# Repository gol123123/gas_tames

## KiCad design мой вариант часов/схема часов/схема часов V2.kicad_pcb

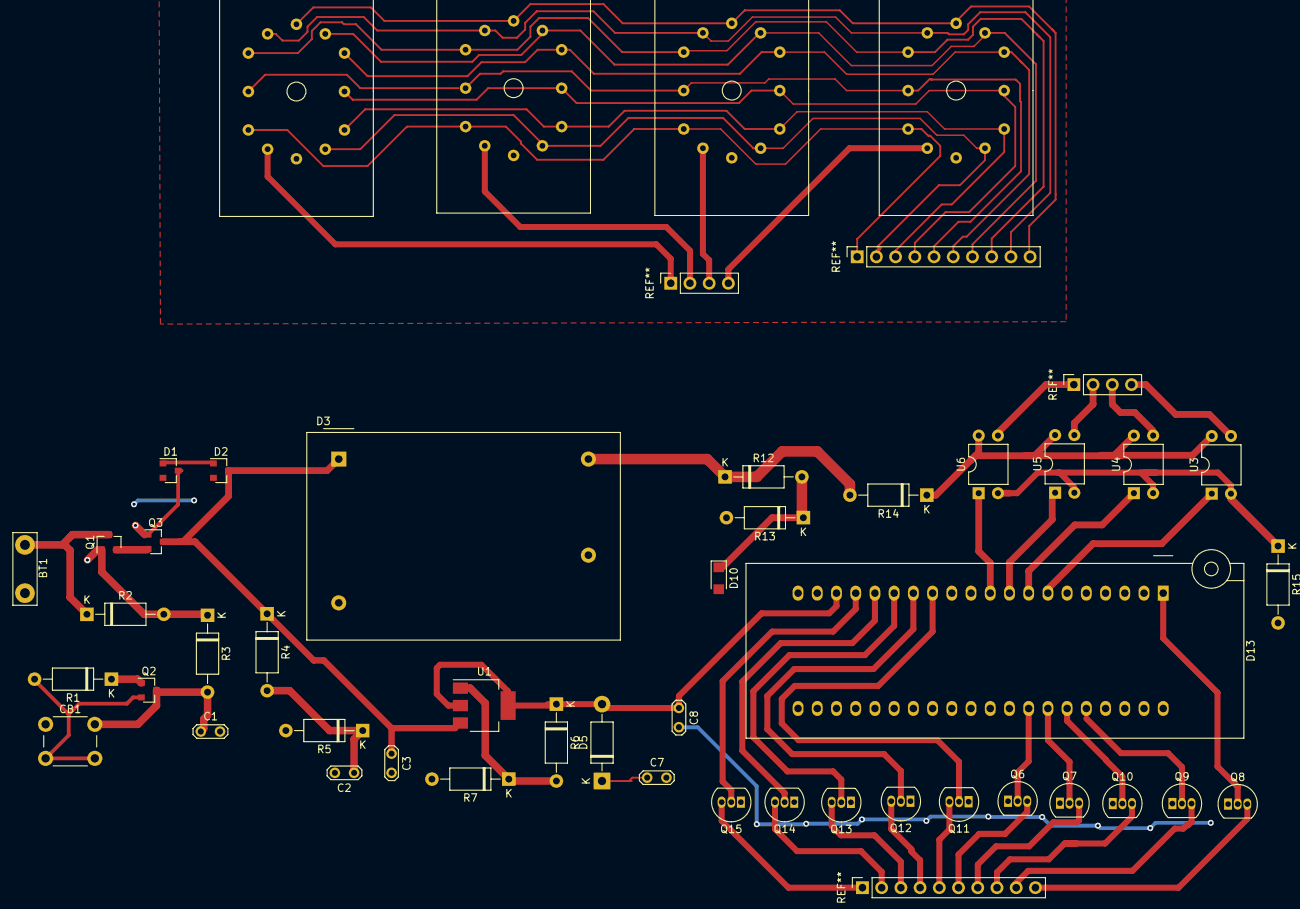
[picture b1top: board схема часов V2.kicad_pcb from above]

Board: 2 copper layers, 46 parts (0 on the bottom side), 43 nets.

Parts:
BT1: Battery_Cell; TestPoint_Bridge_Pitch6.35mm_Drill1.3mm
C1, C2: 100n; TestPoint_2Pads_Pitch2.54mm_Drill0.8mm
C3: 0.1u; TestPoint_2Pads_Pitch2.54mm_Drill0.8mm
C7: 10u; TestPoint_2Pads_Pitch2.54mm_Drill0.8mm
C8: 1u; TestPoint_2Pads_Pitch2.54mm_Drill0.8mm
CB1: CircuitBreaker_1P; SW_PUSH_6mm_H9.5mm
D1, D2: BAT54C; SOT-23
D3: dc-ac_180v; Converter_ACDC_TRACO_TMG-15_THT
D5: 1N4002; D_DO-41_SOD81_P10.16mm_Horizontal
D9, D11, D12, D14: in-12a; IN12
D10: BZD27Cxx; D_SMF
D13: stm32; DIP_Socket-40_W11.9_W12.7_W15.24_W17.78_W18.5_3M_240-1280-0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
Q1, Q3: IRLML6402; SOT-23
Q2: BSS123; SOT-23
Q6, Q7, Q8, Q9, Q10, Q11, Q12, Q13, Q14, Q15: MPSA42; TO-92_Inline
R1, R3, R4, R5: 10k; D_A-405_P10.16mm_Horizontal
R2: 200k; D_A-405_P10.16mm_Horizontal
R6: 4k; D_A-405_P10.16mm_Horizontal
R7: 11k; D_A-405_P10.16mm_Horizontal
R12: 177k; D_A-405_P10.16mm_Horizontal
R13: 3k; D_A-405_P10.16mm_Horizontal
R14: 72k; D_A-405_P10.16mm_Horizontal
R15: 470; D_A-405_P10.16mm_Horizontal
U1: LM317_SOT-223; SOT-223-3_TabPin2
U3, U4, U5, U6: TLP627; DIP-4_W7.62mm

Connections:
+12C: D1.1, D2.1
/KEY: Q2.1, R1.1
/P_PUT: C2.1, R4.2, R5.1
/V: C8.1, D5.2, D13.18, R6.1, U1.2
/V_IND: D10.1, D13.25, R12.2, R13.1
/X0: D13.17, Q15.2
/X1: D13.33, Q6.2
/X2: D13.34, Q7.2
/X3: D13.1, Q8.2
/X4: D13.36, Q9.2
/X5: D13.35, Q10.2
/X6: D13.13, Q11.2
/X7: D13.14, Q12.2
/X8: D13.15, Q13.2
/X9: D13.16, Q14.2
/Y2: D13.8, U4.1
/Y3: D13.9, U5.1
/Y4: D13.10, U6.1
GND: C1.2, C2.2, C3.2, C7.2, C8.2, CB1.2, D1.2, D2.2, D3.2, D3.4, D10.2, D13.19, Q2.2, Q6.1, Q7.1, Q8.1, Q9.1, Q10.1, Q11.1, Q12.1, Q13.1, Q14.1, Q15.1, R1.2, R5.2, R7.2, R13.2, R15.2
unnamed: BT1.1, Q1.3, R2.1
unnamed: C1.1, CB1.1, Q2.3, R3.2
unnamed: C3.1, D2.3, D3.1, Q3.3, R4.1, U1.3
unnamed: C7.1, D5.1
unnamed: D1.3, Q1.1, Q3.1, R2.2, R3.1
unnamed: D3.3, R12.1, R14.2
unnamed: D9.1, U6.3
unnamed: D11.1, U5.3
unnamed: D9.2, D11.2, D12.2, D14.2, Q15.3
unnamed: D9.3, D11.3, D12.3, D14.3, Q14.3
unnamed: D9.4, D11.4, D12.4, D14.4, Q13.3
unnamed: D9.5, D11.5, D12.5, D14.5, Q12.3
unnamed: D9.6, D11.6, D12.6, D14.6, Q11.3
unnamed: D9.7, D11.7, D12.7, D14.7, Q10.3
unnamed: D9.8, D11.8, D12.8, D14.8, Q9.3
unnamed: D9.9, D11.9, D12.9, D14.9, Q8.3
unnamed: D9.10, D11.10, D12.10, D14.10, Q7.3
unnamed: D9.11, D11.11, D12.11, D14.11, Q6.3
unnamed: D12.1, U4.3
unnamed: D14.1, U3.3
unnamed: Q1.2, Q3.2
unnamed: R6.2, R7.1, U1.1
unnamed: R14.1, U3.4, U4.4, U5.4, U6.4
unnamed: D13.7, R15.1, U3.1, U3.2, U4.2, U5.2, U6.2

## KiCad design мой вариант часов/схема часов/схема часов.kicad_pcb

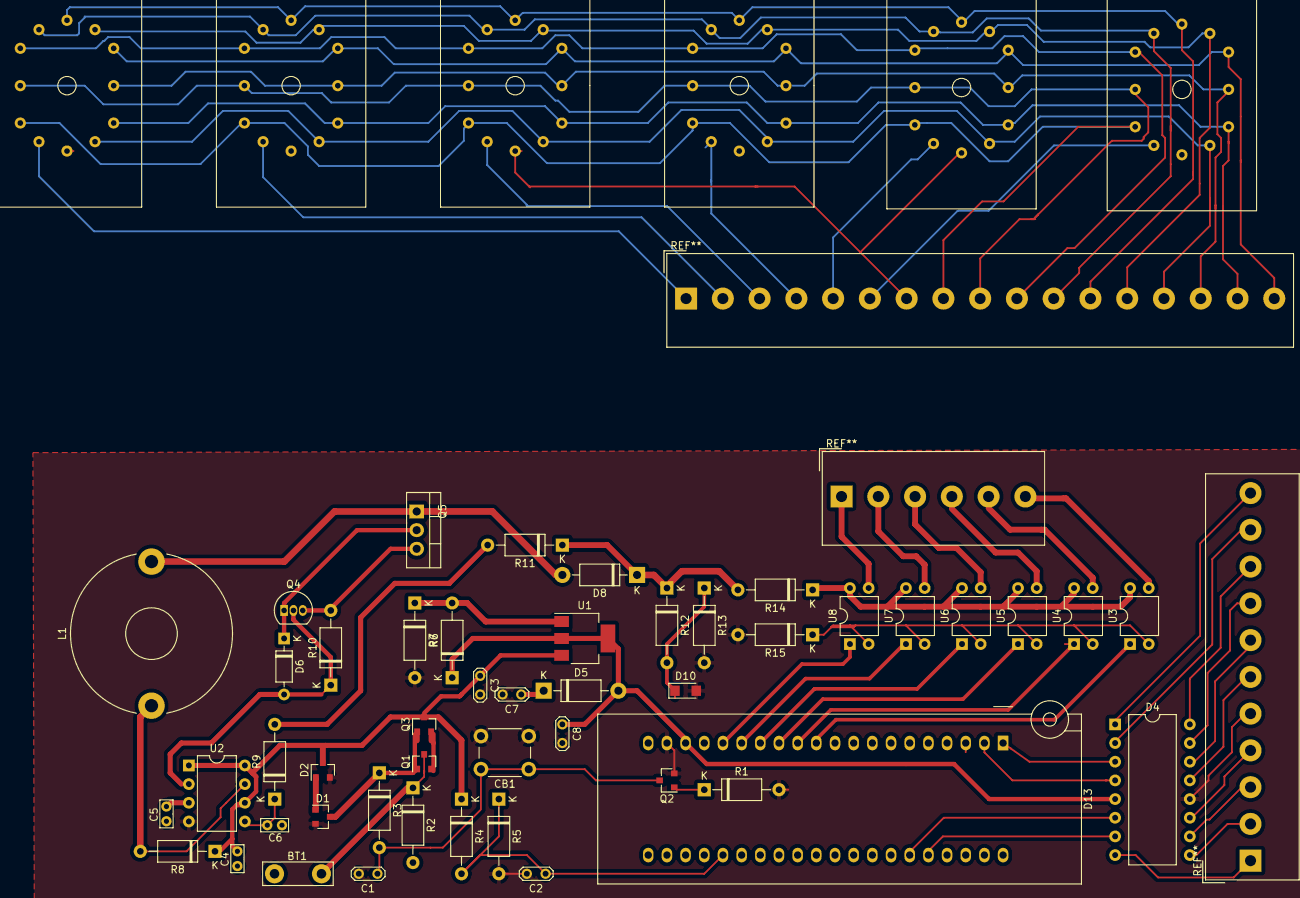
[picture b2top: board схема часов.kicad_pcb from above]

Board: 2 copper layers, 53 parts (0 on the bottom side), 39 nets.

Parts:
BT1: Battery_Cell; TestPoint_Bridge_Pitch6.35mm_Drill1.3mm
C1, C2: 100n; TestPoint_2Pads_Pitch2.54mm_Drill0.8mm
C3: 0.1u; TestPoint_2Pads_Pitch2.54mm_Drill0.8mm
C4: 1000u; TestPoint_Bridge_Pitch2.0mm_Drill0.7mm
C5, C6: 1n; TestPoint_Bridge_Pitch2.0mm_Drill0.7mm
C7: 10u; TestPoint_2Pads_Pitch2.54mm_Drill0.8mm
C8: 1u; TestPoint_2Pads_Pitch2.54mm_Drill0.8mm
CB1: CircuitBreaker_1P; SW_PUSH_6mm_H9.5mm
D1, D2: BAT54C; SOT-23
D3, D7, D9, D11, D12, D14: in-12a; IN12
D4: SN74141N; DIP-16_W10.16mm
D5: 1N4002; D_DO-41_SOD81_P10.16mm_Horizontal
D6: 1N4148; D_DO-35_SOD27_P7.62mm_Horizontal
D8: 1N4007; D_DO-41_SOD81_P10.16mm_Horizontal
D10: BZD27Cxx; D_SMF
D13: stm32; DIP_Socket-40_W11.9_W12.7_W15.24_W17.78_W18.5_3M_240-1280-0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
L1: 230; L_Toroid_Horizontal_D21.8mm_P19.60mm_Bourns_2100
Q1, Q3: IRLML6402; SOT-23
Q2: BSS123; SOT-23
Q4: 2N3906; TO-92_Inline
Q5: IRF840; TO-220-3_Vertical
R1, R3, R4, R5, R10: 10k; D_A-405_P10.16mm_Horizontal
R2: 200k; D_A-405_P10.16mm_Horizontal
R6: 4k; D_A-405_P10.16mm_Horizontal
R7: 11k; D_A-405_P10.16mm_Horizontal
R8: 0.2; D_A-405_P10.16mm_Horizontal
R9, R13: 3k; D_A-405_P10.16mm_Horizontal
R11: 430k; D_A-405_P10.16mm_Horizontal
R12: 177k; D_A-405_P10.16mm_Horizontal
R14: 72k; D_A-405_P10.16mm_Horizontal
R15: 470; D_A-405_P10.16mm_Horizontal
U1: LM317_SOT-223; SOT-223-3_TabPin2
U2: MC34063AP; DIP-8_W7.62mm
U3, U4, U5, U6, U7, U8: TLP627; DIP-4_W7.62mm

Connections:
+12C: D1.1, D2.1
/KEY: D13.17, Q2.1, R1.1
/V: C8.1, D4.5, D5.2, D13.18, R6.1, U1.2
/V_IND_OBR: D10.1, D13.26, R12.2, R13.1
/V_type: C2.1, D13.25, R4.2, R5.1
/X2: D4.6, D13.2
/X3: D4.7, D13.3
/X4: D4.4, D13.4
/Y0: D13.11, U3.1
/Y1: D13.12, U4.1
/Y2: D13.13, U5.1
/Y3: D13.14, U6.1
/Y4: D13.15, U7.1
/Y5: D13.16, U8.1
GND: C1.2, C2.2, C3.2, C7.2, C8.2, CB1.2, D1.2, D2.2, D4.12, D10.2, D13.19, Q2.2, R1.2, R5.2, R7.2, R13.2, R15.2, U2.4
unnamed: BT1.1, Q1.3, R2.1
unnamed: C1.1, CB1.1, Q2.3, R3.2
unnamed: C3.1, C4.1, D2.3, Q3.3, R4.1, R8.1, U1.3, U2.1, U2.6, U2.8
unnamed: C5.1, U2.3
unnamed: C6.1, R9.1, U2.5
unnamed: C7.1, D5.1
unnamed: D1.3, Q1.1, Q3.1, R2.2, R3.1
unnamed: D6.1, Q4.1, Q5.2
unnamed: D6.2, Q4.2, R10.1, U2.2
unnamed: D7.1, U7.3
unnamed: D8.1, R11.1, R12.1, R14.2
unnamed: D8.2, L1.2, Q5.1
unnamed: D9.1, U6.3
unnamed: D11.1, U5.3
unnamed: D3.2, D3.3, D3.4, D3.5, D3.6, D3.7, D3.8, D3.9, D3.10, D3.11, D4.15, D7.2, D7.3, D7.4, D7.5, D7.6, D7.7, D7.8, D7.9, D7.10, D7.11, D9.2, D9.3, D9.4, D9.5, D9.6, D9.7, D9.8, D9.9, D9.10, D9.11, D9.12, D11.2, D11.3, D11.4, D11.5, D11.6, D11.7, D11.8, D11.9, D11.10, D11.11, D12.2, D12.3, D12.4, D12.5, D12.6, D12.7, D12.8, D12.9, D12.10, D12.11, D12.12, D14.2, D14.3, D14.4, D14.5, D14.6, D14.7, D14.8, D14.9, D14.10, D14.11
unnamed: D12.1, U4.3
unnamed: D14.1, U3.3
unnamed: L1.1, R8.2, U2.7
unnamed: Q1.2, Q3.2
unnamed: Q4.3, Q5.3, R10.2
unnamed: R6.2, R7.1, U1.1
unnamed: R9.2, R11.2
unnamed: R14.1, U3.4, U4.4, U5.4, U6.4, U7.4, U8.4
unnamed: R15.1, U3.2, U4.2, U5.2, U6.2, U7.2, U8.2

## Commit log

2020-09-10 second commit
2021-01-16 version-1
